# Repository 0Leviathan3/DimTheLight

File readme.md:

# HACK THE PARADISE - DTL

## Frontend-UI

### Was wir brauchen
- Openstreetmap für alle Lampen
    - Lampen anklickbar
        - Daten über Lampen herausfinden, wenn angeklickt (?)
    - Lampen clustern/entclustern, je nach dem, wie weit man weg ist
- Lampen dimmen
    - slider oder feste Zahlen zum einrasten (30%, 70%)
        - muss man schauen, was die Lampen können
- Regionen festlegen, z.B. Baustelle
    - Eigene Regionen festlegen können
- Login screen
    - Validierung
- Statusinterface der gelesenen Daten
    - aktuell aktive Einstellung vs. im System hinterlegte Einstellung (ist vs soll)
    - evtl. auch mit Historie, um zu sehen, wie sich die Einstellungen über die Zeit verändert haben
    - Timestamps, wann Adapter zuletzt mit LoRaWAN kommuniziert haben
    - (Batteriestatus des Adapters, wenn möglich)
    - Status des Beschreibens des NFC-Chips (erfolgreich oder nicht)

### Wie wir es umsetzen
- Sidebar zum Auswählen was man machen möchte
- Leaflet um Openstreetmap anzuschauen und cluster zu machen
- Authform (vue) für Login
- Daten in GeoJSON vorliegen
    - Koordinatensystem: etrs89
    - Daten mit Python Skript in WGS84 konvertieren, damit sie in Leaflet angezeigt werden können
        - Installation:
            - `sudo apt install python3-py`
            - `sudo apt install python3-pyproj`

- Daten über chirpStack API senden
- API Key liegt unter Tenant -> API Keys
    - Wo ist Unterschied zwischen GRPC_KEY und XXX

- Wir brauchen Daten:
    - astroDim 5 Werte als json senden
    - Helligkeit
    - 3 Keys (chirpStack-intern)
- Daten über LoRaWAN an die Lampen senden

- Es braucht einen Wert 0-100

Notiz an Dennis (Server starten):    HOST=0.0.0.0 pnpm run dev

# Hack The Paradise - Dim The Light

## Beschreibung
*Die Software für das Projekt "Dim The Light" ist eine webbasierte Dashboard-Lösung für eine simple Steuerung und Verwaltung von Straßenlaternen in der Stadt Jena über das LoRaWAN-Netzwerk. Die Helligkeit der Lampen lässt sich eizeln oder gruppiert (Region) über das entwickelte Softwaresystem und den pysischen Adapter einstellen und speichern. Die Software kommuniziert mir dem Jenaer ChirpStack-Server, die als API Schnittstelle zum LoRaWAN-Netzwerk dient. Der Adapter Verbindet das LoRaWAN-Netzwerk über einen Raspberry Pi Pico mit dem integrierten NFC-Modul. Dises beschreibt und ließt von dem OSRAM-Netzteil.*

anzeigen zu lassen, konkrete Straßenlampen nach ihren Jena Leuchtstellen-Nummer zu suchen (z.B. 001-001)

## Systemarchitektur
```
Browser (Vue 3 / Nuxt 4)
    | HTTP / Fetch
Nuxt Nitro Server (Node.js)
    | SQLite (Nitro built-in)
    | gRPC-Web über HTTPS
ChirpStack LoRaWAN Server (chirpstack.jena.de)
    | LoRaWAN Funknetz
Straßenlaternen-Adapter (mit dev_eui)
```

## Features
### Interaktive Karte
- Anzeigen aller Laternenpunkte via Leaflet.js inklusive Marker-Clustering.
- einzelne Laternen ansteuern via klick
- Helligkeiten können über Dashboard eingestellt und gespeichert werden

### LoRaWAN-Sync
- Übertragung von Helligkeitswerten als 1-Byte-Payload über gRPC-Web an ChirpStack

### Regionen-Steuerung
-  man kann Regionen definieren durch Freihand-Auswahl, um mehrere Lampen gleichzeitig anzusteuern und Helligkeitswerte zu setzen

### Soll/Ist-Vergleich
- Falls Anpassungen vorliegen werden diese mit den aktuellen Werten verglichen, um ausschließlich neue Werte zu übertragen.

## Getting Started
t.b.d
### Voraussetzungen
t.b.d

### Umgebungsvariablen
t.b.d

### Installation & Datenaufbereitung
t.b.d

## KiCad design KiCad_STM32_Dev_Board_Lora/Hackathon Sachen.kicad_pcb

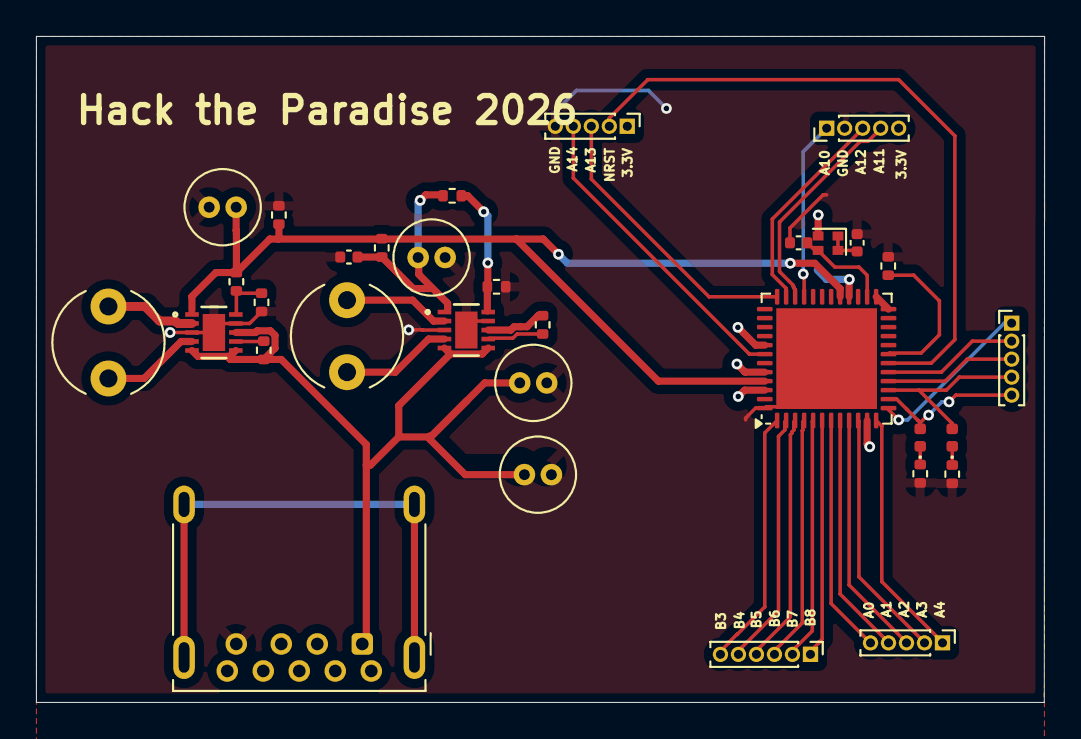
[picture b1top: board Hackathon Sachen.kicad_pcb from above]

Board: 2 copper layers, 56.0 x 37.0 mm, 32 parts (0 on the bottom side), 39 nets.

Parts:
C1, C2: 10n; C_0402_1005Metric
C3: 100n; C_0402_1005Metric
C4, C5: 10u; C_Radial_D4.0mm_H7.0mm_P1.50mm
C6, C7: 20u; C_Radial_D4.0mm_H7.0mm_P1.50mm
D1, D2: LED; LED_0402_1005Metric
J1: USB3_A; USB3_A_Molex_48393-001
J2, J3, J5, J6: Conn_01x05_Pin; PinHeader_1x05_P1.00mm_Vertical
J7: Conn_01x06_Pin; PinHeader_1x06_P1.00mm_Vertical
L1: 2.2u; L_Radial_D6.0mm_P4.00mm
L2: 4.7u; L_Radial_D6.0mm_P4.00mm
R1, R2, R7: 100; R_0402_1005Metric
R3: 10k; R_0402_1005Metric
R4: 487k; R_0402_1005Metric
R5: 86.6k; R_0402_1005Metric
R6, R7#2, R8#2: 100k; R_0402_1005Metric
R8: 90; R_0402_1005Metric
R9: 210k; R_0402_1005Metric
U1, U3: RT6150B-33GQW; 10-WFDFN-EP_RIT
U2: STM32WLE5C8Ux; QFN-48-1EP_7x7mm_P0.5mm_EP5.6x5.6mm
Y2: 32MHz; Oscillator_SMD_Abracon_ASCO-4Pin_1.6x1.2mm

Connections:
1.55V: C7.1, R7.2, R8.1, R9.2, U2.29 (VDDRF1V55), U2.45 (VFBSMPS), U3.1 (VOUT)
3.3V: C3.2, C6.2, J2.5, J3.1, R4.2, R7.1, U1.1 (VOUT), U2.11 (VDD), U2.24 (VR_PA), U2.25 (VDDPA), U2.28 (VDDRF), U2.41 (VDDA), U2.44 (VDD), U2.46 (VDDSMPS), Y2.2
5V: C4.2, C5.1, J1.1 (VBUS), R6.2, R8#2.2, U1.5 (VIN), U1.6 (EN), U1.8 (VINA), U3.5 (VIN), U3.6 (EN), U3.8 (VINA)
GND: C1.2, C2.2, C3.1, C4.1, C5.2, C6.1, C7.2, J1.4 (GND), J2.2, J3.5, R1.1, R2.2, R3.1, R5.1, R7#2.1, R8.2, U1.3 (GND), U1.9 (GND), U1.11 (GND), U2.48 (VSSSMPS), U2.49 (VSS), U3.3 (GND), U3.9 (GND), U3.11 (GND)
MISO SPI1: J2.4, U2.34 (PA11)
MOSI SPI1: J2.3, U2.35 (PA12)
NRST: J3.2, U2.18 (NRST)
unnamed: C2.1, Y2.1, Y2.4
unnamed: D1.2 (A), J5.5, U2.14 (PA6)
unnamed: D1.1 (K), R1.2
unnamed: D2.2 (A), J5.4, U2.15 (PA7)
unnamed: D2.1 (K), R2.1
unnamed: J2.1, U2.33 (PA10)
unnamed: J5.2, U2.17 (PA9)
unnamed: J5.3, U2.16 (PA8)
unnamed: J6.1, U2.12 (PA4)
unnamed: J6.2, U2.10 (PA3)
unnamed: J6.3, U2.9 (PA2)
unnamed: J6.4, U2.8 (PA1)
unnamed: J6.5, U2.7 (PA0)
unnamed: J7.1, U2.6 (PB8)
unnamed: J7.2, U2.5 (PB7)
unnamed: J7.3, U2.4 (PB6)
unnamed: J7.4, U2.3 (PB5)
unnamed: J7.5, U2.2 (PB4)
unnamed: J7.6, U2.1 (PB3)
unnamed: R4.1, R5.2, U1.10 (FB)
unnamed: L1.1, U1.4 (LX1)
unnamed: L1.2, U1.2 (LX2)
unnamed: R6.1, U1.7 (PS)
unnamed: R3.2, U2.19 (PH3)
unnamed: R7#2.2, R9.1, U3.10 (FB)
unnamed: L2.1, U3.4 (LX1)
unnamed: L2.2, U3.2 (LX2)
unnamed: R8#2.1, U3.7 (PS)
OSC_IN: C1.1, U2.26 (OSC_IN), Y2.3
SCK SPI1: J5.1, U2.13 (PA5)
SWCK: J3.4, U2.42 (PA14)
swd: J3.3, U2.36 (PA13)

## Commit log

2026-06-13 Add: Grundgerüst website
2026-06-13 Hoffentlich genug
2026-06-13 piko Bib
2026-06-13 Funktonierendes MVP Website
2026-06-13 Readme
2026-06-13 Rename main to main.py
2026-06-13 add pcb design
